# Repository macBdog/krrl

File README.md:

# KRRL-01

Control software and operator UI for the KRRL-01 vinyl record lathe.

**Hardware:** Raspberry Pi 4 (brain + audio + camera) and Arduino Mega 2560 (real-time motors and IO).  
**OS:** Raspberry Pi OS Lite 64-bit (Debian). See [docs/OS.md](docs/OS.md).

The Pi never generates step pulses. The Mega owns platter, X (lead screw), Z (depth), heated stylus PID, chip vacuum, limits, and E-stop.

## Quick start (desktop, no hardware)

```bash
cd krrl-01
PYTHONPATH=host python3 -m krrl --dry-run --port 8080
```

Open http://127.0.0.1:8080 — Live, Experiment, Cut, and Setup all run against a Mega simulator.

```bash
PYTHONPATH=host python3 -m krrl.check
```

## Pi (with Mega)

1. Flash **Raspberry Pi OS Lite 64-bit**.
2. Run `sudo bash deploy/tune-pi.sh`.
3. Copy this tree to `/opt/krrl-01`.
4. `sudo cp deploy/krrl.service /etc/systemd/system && sudo systemctl enable --now krrl`
5. Connect the Mega on USB (`/dev/ttyACM0`). I2S DAC HAT for the cutter amp; not the 3.5 mm jack.

## Layout

| Path | Role |
|------|------|
| `firmware/krrl_mega/` | Mega 2560 sketch (lathe) |
| `firmware/krrl_player/` | Nano sketch (player turntable variant) |
| `host/krrl/` | Python host |
| `ui/` | Operator console |
| `config/machine.yaml` | Calibration and devices |
| `docs/PROTOCOL.md` | Serial line protocol |
| `docs/PLAYER.md` | Player turntable variant |
| `docs/TACHOMETER.md` | Optional optical index monitor + marking/machining |
| `docs/CALIBRATION.md` | Open-loop platter speed calibration |
| `hardware/` | Drive/bearing/belt/stepper/phono notes + BOM |
| `deploy/` | systemd, PipeWire, OS tune |

## Player variant

A lower-cost, playback-only turntable on an **Arduino Nano only** (no Pi, no UI):
33/45/78 with ±8% pitch and start/stop, reusing the lathe belt drive, TMC2209
driver and motion core. See [docs/PLAYER.md](docs/PLAYER.md).

## Cut v1

Constant pitch only. Groove feed is `mm/s = rpm/60 * (25.4 / lpi)`. Variable-pitch preview is reserved for v2.

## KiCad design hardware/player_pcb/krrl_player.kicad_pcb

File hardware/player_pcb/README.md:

# Player mainboard (KiCad)

A single fabricable 2-layer PCB that carries the whole player turntable
electronics: the **Arduino Nano**, a **TMC2209** stepper-driver module, the
**RIAA phono preamp**, and all **front-panel I/O**. Speed is open-loop
feedforward (see [`docs/CALIBRATION.md`](../../docs/CALIBRATION.md)); the board
has no speed sensor.

Open in KiCad 7+: `krrl_player.kicad_pro` (board `krrl_player.kicad_pcb`). It is a
**standalone board** (no schematic sheet) — every connection is defined by the
board nets, tabulated below and in [`NETLIST.txt`](NETLIST.txt).

## Board sections

- **Left:** analog phono — cartridge input `J_CART`, `NE5532` (`U2`), the RIAA
  network, and line output `J_OUT`.
- **Centre/right:** digital — the Nano (`J1`/`J2`) and the TMC2209 module (`M1`).
- **Right edge:** power/motor terminals (`J_PM`, `J_PL`, `J_MOT`).
- **Front edge:** controls — mode button `SW1`, speed pot `RV1`, RGB mode LED
  `D_RGB`, power LED `D_PWR`.

The analog section sits at the opposite end from the motor terminal and TMC to
keep the 5 mV cartridge signal away from stepper switching (see
[`hardware/phono.md`](../phono.md) for the EMI/grounding rationale).

## Power supply (external, separate — specify when ordering the PSU)

The board has **no on-board regulators**; it expects an external multi-rail
supply. A linear analog rail keeps the phono stage quiet.

| Rail | Use | Min current | Enters at |
|------|-----|-------------|-----------|
| +24 V | Stepper (TMC `VMOT`) | ~1.5 A | `J_PM` pin 1 |
| +5 V | Logic (Nano, TMC `VIO`, LEDs) | ~0.5 A | `J_PL` pin 1 |
| +12 V | Phono op-amp V+ | ~50 mA | `J_PL` pin 2 |
| −12 V | Phono op-amp V− | ~50 mA | `J_PL` pin 3 |
| GND | Common return | — | `J_PM` pin 2, `J_PL` pin 4 |

All grounds meet at the board (single GND pour = star point). Keep the PSU's
motor return and analog return joined only at the supply to avoid a ground loop.
±12 V may be ±15 V if preferred (NE5532 max ±22 V).

## Connectors

**`J_PM` — 24 V motor power** (2-pos): 1 = +24 V, 2 = GND.
**`J_PL` — logic/analog power** (4-pos): 1 = +5 V, 2 = +12 V, 3 = −12 V, 4 = GND.
**`J_MOT` — stepper motor** (4-pos): 1 = 2B, 2 = 2A, 3 = 1A, 4 = 1B (coil pairs
1A/1B and 2A/2B).
**`J_CART` — cartridge in** (1×5): 1 = L-hot, 2 = L-gnd, 3 = R-hot, 4 = R-gnd,
5 = shield (2/4/5 → GND).
**`J_OUT` — line out** (1×3): 1 = L, 2 = GND, 3 = R (fit an RCA pigtail).

## Front panel

| Control | Part | Wiring |
|---------|------|--------|
| Mode button | `SW1` momentary | to `MODE` (Nano D6, `INPUT_PULLUP`) and GND |
| Speed pot | `RV1` 10k lin | 1 → GND, 2 (wiper) → A0, 3 → +5 V |
| Mode LED | `D_RGB` common-cathode | R/G/B anodes via `R_R`/`R_G`/`R_B` → D9/D10/D11; cathode → GND |
| Power LED | `D_PWR` | +5 V → `R_PWR` → anode; cathode → GND |

RGB colours (firmware): off = stopped, green = 33, blue = 45, red = 78; blinks
while spinning up, solid at speed.

## Nano pin usage (`J1` side A, `J2` side B)

| Net | Nano pin | Header |
|-----|----------|--------|
| +5 V | 5V | J1.12 |
| GND | GND | J1.14, J2.12 |
| Speed pot wiper | A0 | J1.4 |
| STEP | D3 | J2.10 |
| DIR | D4 | J2.9 |
| EN | D5 | J2.8 |
| MODE | D6 | J2.7 |
| LED R / G / B | D9 / D10 / D11 | J2.4 / J2.3 / J2.2 |
| TMC UART (opt.) | D1 TX / D0 RX | J2.15 / J2.14 |

## TMC2209 module header (`M1`, 2×8)

Follows the StepStick / A4988-compatible layout so a SilentStepStick-class
TMC2209 mounts here. **Verify your module's pinout — especially the PDN/UART
pin — before soldering.**

| Pin | Net | Pin | Net |
|----:|-----|----:|-----|
| 1 | EN | 2 | +24 V (VMOT) |
| 3 | MS1 → +5 V | 4 | GND |
| 5 | MS2 → +5 V | 6 | 2B |
| 7 | PDN/UART | 8 | 2A |
| 9 | (nc) | 10 | 1A |
| 11 | (nc) | 12 | 1B |
| 13 | STEP | 14 | +5 V (VIO) |
| 15 | DIR | 16 | GND |

`MS1`/`MS2` are tied to +5 V for **1/16 microstepping** in standalone STEP/DIR
mode (matches the firmware `steps_per_rev = 3200`). For the optional UART build
(`-DTMC_UART`), the Nano UART reaches `PDN` via `R_UART` (1 k); set the module
address as needed.

## RIAA phono

One `NE5532` (`U2`) as two non-inverting active-feedback RIAA stages. Per-channel
values and the design rationale are in [`hardware/phono.md`](../phono.md):
47 k∥100 pF load, `R_A` 100 k / `C_A` 33 n / `R_B` 7.5 k / `C_B` 10 n feedback,
`R_G` 1 k + `C_G` 100 µF gain-set, `R_O` 100 Ω + `C_O` 3.3 µF output. Treat the
values as a verified-by-calculator starting point.

## Board specs / fabrication

- **2-layer** FR4, 1.6 mm, 1 oz copper; **140 × 110 mm**.
- Design rules: 0.2 mm track / 0.2 mm clearance; vias 0.8 mm / 0.4 mm; GND pours
  on both layers.
- Fab outputs: [`gerbers/`](gerbers) (RS-274X + Excellon `.drl`) and
  [`krrl_player_gerbers.zip`](krrl_player_gerbers.zip). BOM in
  [`BOM.csv`](BOM.csv).

### Regenerate

The board is generated from source (KiCad 7 `pcbnew` + freerouting):

```
FREEROUTING_JAR=/path/to/freerouting-1.9.0.jar ./route.sh   # place + net + autoroute
./fab.sh                                                    # gerbers + drill + renders
```

`build_pcb.py` is the source of truth for components and connections; edit it and
re-run to change the design.

## Status / caveats

- **Fully routed, 0 unrouted connections** at the rules above; placement and
  routing are auto-generated (freerouting) — review in KiCad before ordering.
- Verify the **TMC2209 module** and **RGB LED** pinouts against your exact parts.
- RIAA values and the external PSU rails should be confirmed for your build.
- This is a design deliverable validated by connectivity + Gerber export; it has
  **not been fabricated or bench-tested**.

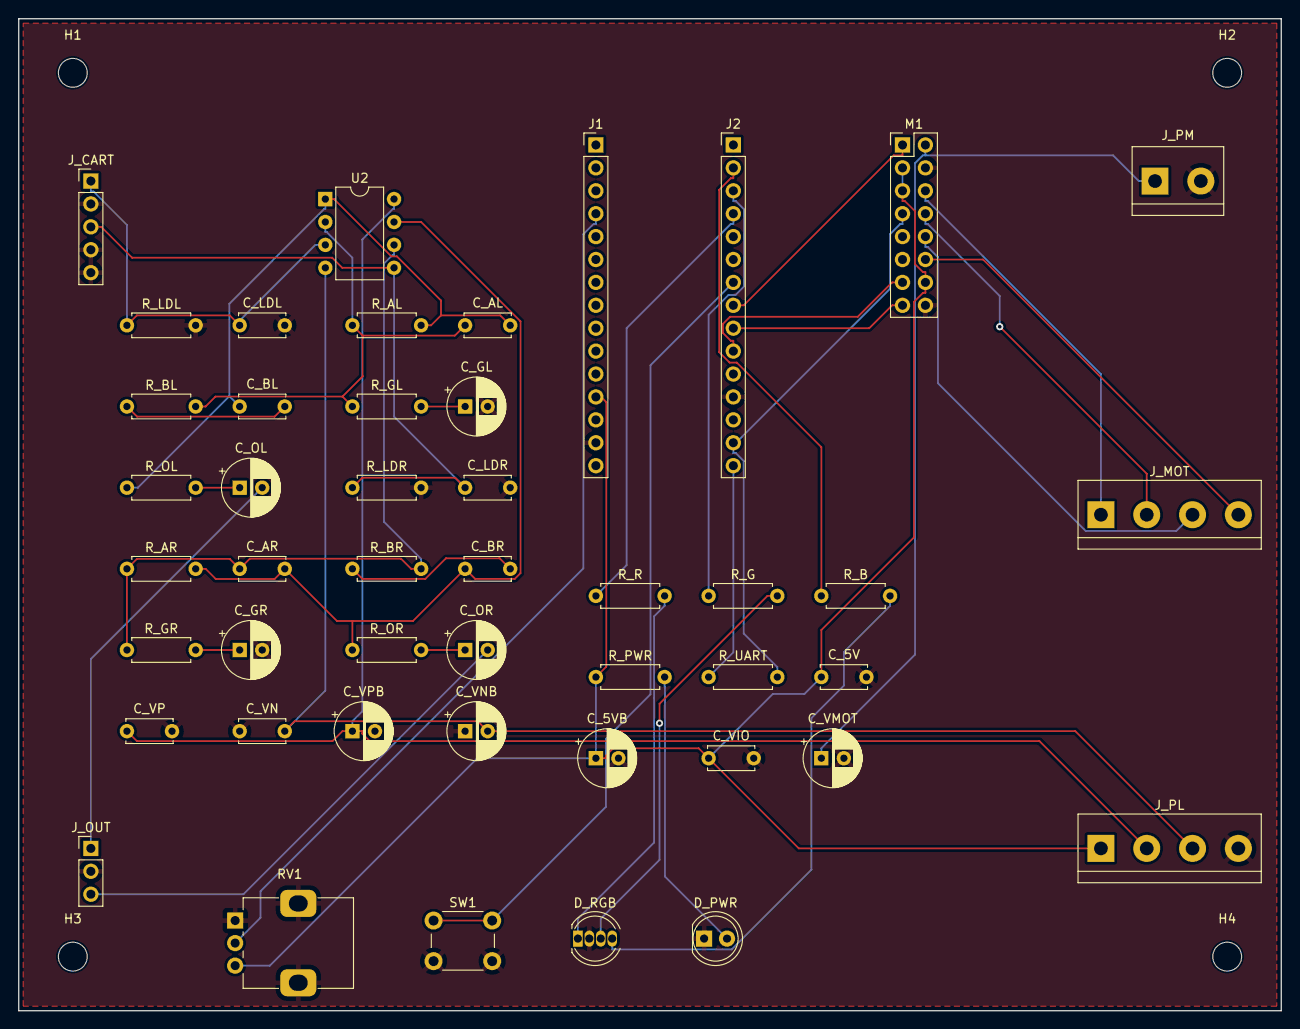
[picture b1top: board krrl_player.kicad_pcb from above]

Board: 2 copper layers, 140.0 x 110.0 mm, 50 parts (0 on the bottom side), 37 nets.

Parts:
C_5V: 100n; C_Disc_D5.0mm_W2.5mm_P5.00mm
C_5VB: 10u; CP_Radial_D6.3mm_P2.50mm
C_AL: 33n; C_Disc_D5.0mm_W2.5mm_P5.00mm
C_AR: 33n; C_Disc_D5.0mm_W2.5mm_P5.00mm
C_BL: 10n; C_Disc_D5.0mm_W2.5mm_P5.00mm
C_BR: 10n; C_Disc_D5.0mm_W2.5mm_P5.00mm
C_GL: 100u; CP_Radial_D6.3mm_P2.50mm
C_GR: 100u; CP_Radial_D6.3mm_P2.50mm
C_LDL: 100p; C_Disc_D5.0mm_W2.5mm_P5.00mm
C_LDR: 100p; C_Disc_D5.0mm_W2.5mm_P5.00mm
C_OL: 3u3; CP_Radial_D6.3mm_P2.50mm
C_OR: 3u3; CP_Radial_D6.3mm_P2.50mm
C_VIO: 100n; C_Disc_D5.0mm_W2.5mm_P5.00mm
C_VMOT: 100u; CP_Radial_D6.3mm_P2.50mm
C_VN: 100n; C_Disc_D5.0mm_W2.5mm_P5.00mm
C_VNB: 10u; CP_Radial_D6.3mm_P2.50mm
C_VP: 100n; C_Disc_D5.0mm_W2.5mm_P5.00mm
C_VPB: 10u; CP_Radial_D6.3mm_P2.50mm
D_PWR: POWER; LED_D5.0mm
D_RGB: RGB_MODE; LED_D5.0mm-4_RGB
H1, H2, H3, H4: M3; MountingHole_3.2mm_M3
J1: Nano_A; PinHeader_1x15_P2.54mm_Vertical
J2: Nano_B; PinHeader_1x15_P2.54mm_Vertical
J_CART: CART_IN; PinHeader_1x05_P2.54mm_Vertical
J_MOT: MOTOR; TerminalBlock_bornier-4_P5.08mm
J_OUT: LINE_OUT; PinHeader_1x03_P2.54mm_Vertical
J_PL: PWR_5V_12V; TerminalBlock_bornier-4_P5.08mm
J_PM: PWR_24V; TerminalBlock_bornier-2_P5.08mm
M1: TMC2209; PinHeader_2x08_P2.54mm_Vertical
RV1: 10k_SPEED; Potentiometer_Alps_RK09K_Single_Vertical
R_AL: 100k; R_Axial_DIN0207_L6.3mm_D2.5mm_P7.62mm_Horizontal
R_AR: 100k; R_Axial_DIN0207_L6.3mm_D2.5mm_P7.62mm_Horizontal
R_B: 220R; R_Axial_DIN0207_L6.3mm_D2.5mm_P7.62mm_Horizontal
R_BL: 7k5; R_Axial_DIN0207_L6.3mm_D2.5mm_P7.62mm_Horizontal
R_BR: 7k5; R_Axial_DIN0207_L6.3mm_D2.5mm_P7.62mm_Horizontal
R_G: 220R; R_Axial_DIN0207_L6.3mm_D2.5mm_P7.62mm_Horizontal
R_GL: 1k; R_Axial_DIN0207_L6.3mm_D2.5mm_P7.62mm_Horizontal
R_GR: 1k; R_Axial_DIN0207_L6.3mm_D2.5mm_P7.62mm_Horizontal
R_LDL: 47k; R_Axial_DIN0207_L6.3mm_D2.5mm_P7.62mm_Horizontal
R_LDR: 47k; R_Axial_DIN0207_L6.3mm_D2.5mm_P7.62mm_Horizontal
R_OL: 100R; R_Axial_DIN0207_L6.3mm_D2.5mm_P7.62mm_Horizontal
R_OR: 100R; R_Axial_DIN0207_L6.3mm_D2.5mm_P7.62mm_Horizontal
R_PWR: 1k; R_Axial_DIN0207_L6.3mm_D2.5mm_P7.62mm_Horizontal
R_R: 330R; R_Axial_DIN0207_L6.3mm_D2.5mm_P7.62mm_Horizontal
R_UART: 1k; R_Axial_DIN0207_L6.3mm_D2.5mm_P7.62mm_Horizontal
SW1: MODE; SW_PUSH_6mm
U2: NE5532; DIP-8_W7.62mm

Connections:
+5V: C_5V.1, C_5VB.1, C_VIO.1, J1.12, J_PL.1, M1.3, M1.5, M1.14, RV1.3, R_PWR.1
+12V: C_VP.1, C_VPB.1, J_PL.2, U2.8
+24V: C_VMOT.1, J_PM.1, M1.2
-12V: C_VN.2, C_VNB.2, J_PL.3, U2.4
BML: C_BL.2, R_BL.1
BMR: C_BR.2, R_BR.1
DIR: J2.9, M1.15
EN: J2.8, M1.1
FBL: C_AL.1, R_AL.1, R_BL.2, R_GL.1, U2.2
FBR: C_AR.1, R_AR.1, R_BR.2, R_GR.1, U2.6
GML: C_GL.1, R_GL.2
GMR: C_GR.1, R_GR.2
GND: C_5V.2, C_5VB.2, C_GL.2, C_GR.2, C_LDL.2, C_LDR.2, C_VIO.2, C_VMOT.2, C_VN.1, C_VNB.1, C_VP.2, C_VPB.2, D_PWR.1, D_RGB.2, J1.14, J2.12, J_CART.2, J_CART.4, J_CART.5, J_OUT.2, J_PL.4, J_PM.2, M1.4, M1.16, RV1.1, RV1.MP, R_LDL.2, R_LDR.2, SW1.2
INL: C_LDL.1, J_CART.1, R_LDL.1, U2.3
INR: C_LDR.1, J_CART.3, R_LDR.1, U2.5
LEDB: J2.2, R_B.1
LEDG: J2.3, R_G.1
LEDR: J2.4, R_R.1
LOUTL: C_OL.2, J_OUT.1
LOUTR: C_OR.2, J_OUT.3
M1A: J_MOT.3, M1.10
M1B: J_MOT.4, M1.12
M2A: J_MOT.2, M1.8
M2B: J_MOT.1, M1.6
MODE: J2.7, SW1.1
OLL: C_OL.1, R_OL.2
OLR: C_OR.1, R_OR.2
OUTL: C_AL.2, C_BL.1, R_AL.2, R_OL.1, U2.1
OUTR: C_AR.2, C_BR.1, R_AR.2, R_OR.1, U2.7
PDN: J2.14, M1.7, R_UART.2
POTW: J1.4, RV1.2
PWRA: D_PWR.2, R_PWR.2
RGB_B: D_RGB.4, R_B.2
RGB_G: D_RGB.3, R_G.2
RGB_R: D_RGB.1, R_R.2
STEP: J2.10, M1.13
TX: J2.15, R_UART.1
